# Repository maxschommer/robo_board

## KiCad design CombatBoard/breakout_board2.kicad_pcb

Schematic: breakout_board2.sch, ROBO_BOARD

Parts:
BTN1: CKN10291CT-ND; KMT071_NGJ_LHS
C1, C2: 10pF; C_0603
C3, C5, C13, C14, C15, C16: 1uF; C_0603
C4: 4.7uF, 16V; C_0805
C6: .1uF; C_0603
C7, C9, C10: 100nF; C_0603
C8, C11, C12: 10uF; C_0805
J1, J2: Conn_01x15; Pin_Header_Straight_1x15_Pitch2.54mm
J3: CONN_02x04; Pin_Header_Straight_2x04_Pitch2.54mm_SMD
J4: CONN_01X03; Pin_Header_Straight_1x03_Pitch2.54mm
J5: Conn_02x03_Odd_Even; Pin_Header_Straight_2x03_Pitch2.54mm
J6: Conn_01x02; Pin_Header_Straight_1x02_Pitch2.54mm
J7: Conn_01x04; Pin_Header_Straight_1x04_Pitch2.54mm
LED1: RED; LED_0805
LED2: GREEN; LED_0805
LED3: BLUE; LED_0805
OS1: 16MHZ; XC2119CT
R1: 10K; R_0603
R2, R3, R4: 499; R_0603
U1: ATMEGA328P-MUR; QFN-32-1EP_5x5mm_Pitch0.5mm
U2: TB6612FNG; SOP65P760X160-24N
U3: ADP3330; SOT-23-6
U4: LP5907SNX-3.3/NOPB; DQN4

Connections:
+3V3: C7.1, C8.1, C16.1, J2.14, J3.7 (Pin_4), U4.1
+5V: C3.2, C4.2, C5.2, C10.1, C12.1, C13.1, C15.1, J2.4, J5.2, R1.1, R4.2, U1.4, U1.6, U1.18, U2.15, U2.20, U2.23, U3.1, U4.3, U4.4
+12V: C9.1, C11.1, C14.1, J2.1, J6.1, U2.13, U2.14, U2.24, U3.2, U3.6
/A0: J2.12, U1.23
/A1: J2.11, U1.24
/A2: J2.10, U1.25
/A3: J2.9, U1.26
/A4: J2.8, U1.27
/A5: J2.7, U1.28
/A6: J2.6, U1.19
/A7: J2.5, U1.22
/AREF: C6.2, J2.13, U1.20
/D0: J1.2, U1.30
/D1: J1.1, U1.31
/D2: J1.5, R2.2, U1.32
/D3: J1.6, U1.1, U2.16
/D4: J1.7, U1.2
/D5: J1.8, U1.9, U2.17
/D6: J1.9, U1.10, U2.22
/D7: J1.10, J3.6, U1.11
/D8: J1.11, J3.5 (Pin_3), U1.12
/D9: J1.12, U1.13, U2.21
/D10: J1.13, J4.3, U1.14
/D11/MOSI: J1.14, J3.3 (Pin_2), J5.4, U1.15
/D12/MISO: J1.15, J3.2 (Pin_8), J5.1, U1.16
/D13/SCK: J2.15, J3.4 (Pin_7), J5.3, R3.1, U1.17
/M1A: J7.4, U2.11, U2.12
/M1B: J7.3, U2.7, U2.8
/M2A: J7.2, U2.5, U2.6
/M2B: J7.1, U2.1, U2.2
/RESET: BTN1.2, J1.3, J2.3, J5.5, R1.2, U1.29, U2.19
GND: BTN1.3, C1.2, C2.2, C3.1, C4.1, C5.1, C6.1, C7.2, C8.2, C9.2, C10.2, C11.2, C12.2, C13.2, C14.2, C15.2, C16.2, J1.4, J2.2, J3.8 (Pin_5), J4.1, J5.6, J6.2, LED1.1, LED2.1, LED3.1, OS1.2, OS1.4, U1.3, U1.5, U1.21, U1.33, U2.3, U2.4, U2.9, U2.10, U2.18, U3.4, U4.2, U4.5
unnamed: C1.1, OS1.1, U1.8
unnamed: C2.1, OS1.3, U1.7
unnamed: LED1.2, R3.2
unnamed: LED2.2, R2.1
unnamed: LED3.2, R4.1

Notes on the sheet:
BLDC HEADER
NRF24L01 HEADER
ICSP HEADER
5V REGULATOR
3V3 REGULATOR
DC MOTOR CONTROLLER
MICROCONTROLLER
VIN
POWER LED
RADIO LED

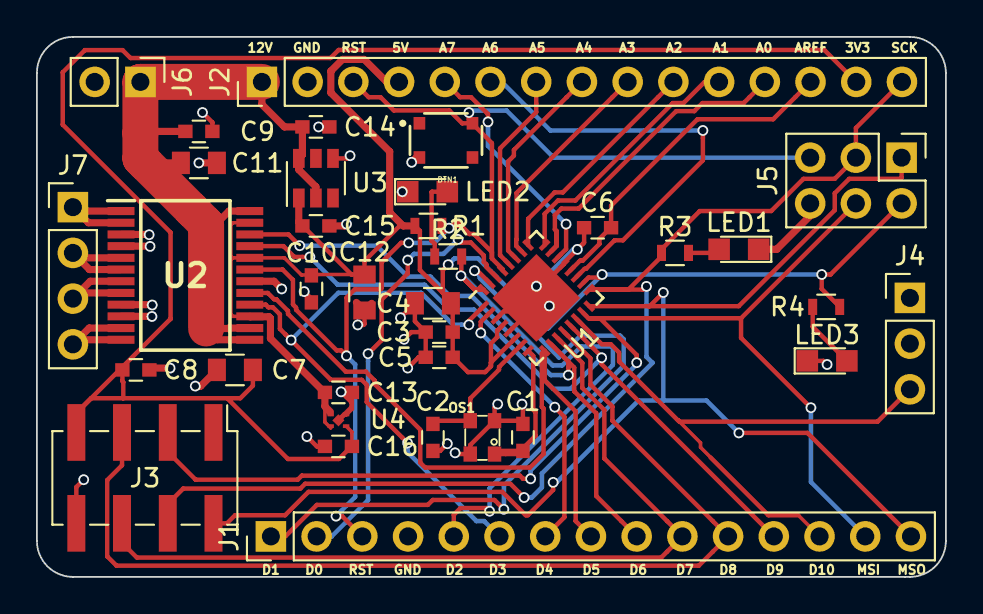
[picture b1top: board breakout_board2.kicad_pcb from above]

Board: 2 copper layers, 50.5 x 30.0 mm, 36 parts (0 on the bottom side), 37 nets.

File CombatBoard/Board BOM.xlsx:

Component | Description | Part | References | Value | Digikey P/N | Quantity Per PCB | Cost | Line Cost
1.0 | Reset Button | button | BTN1 | CKN10291CT-ND | CKN10291CT-ND | 1.0 | 0.3 | 0.3
2.0 | Unpolarized capacitor , .1uf | C | C6 C7 C9 C10 | .1uF | 445-5667-1-ND | 4.0 | 0.1 | 0.4 | 311-1779-1-ND
3.0 | Unpolarized capacitor, 10pf | C | C1 C2 | 10pF | 490-9682-1-ND | 2.0 | 0.15 | 0.3
4.0 | Unpolarized capacitor, 10uf | C | C8 C11 C12 | 10uF | 445-5667-1-ND | 3.0 | 0.28 | 0.84 | 1276-2872-1-ND
5.0 | Unpolarized capacitor, 1uf | C | C3 C5 C13 C14 C15 C16 | 1uF | 399-7376-1-ND | 6.0 | 0.24 | 1.44
6.0 | Unpolarized capacitor,16v 4.7uf | C | C4 | 4.7uF, 16V | 587-4877-1-ND | 1.0 | 0.34 | 0.34
7.0 | BLDC Pin Header | Conn_01x03 | J4 | CONN_01X03 | S5674-ND | 1.0 | 1.14 | 1.14
8.0 | Radio Pin HEader | Conn_02x04_Counter_Clockwise-RESCUE-breakout_board | J3 | CONN_02x04 | ----- | 1.0 | 0.0 | 0
9.0 | ICSP Pin Header | Conn_02x03_Odd_Even | J5 | Conn_02x03_Odd_Even | ------ | 1.0 | 0.0 | 0
10.0 | LED generic | LED | LED3 | BLUE | 160-1579-1-ND | 1.0 | 0.43 | 0.43
11.0 | LED generic | LED | LED2 | GREEN | 160-1887-1-ND | 1.0 | 0.65 | 0.65
12.0 | LED generic | LED | LED1 | RED | 160-1427-1-ND | 1.0 | 0.31 | 0.31
13.0 | 16MHZ Oscillator | Crystal_GND24 | OS1 | 16MHZ | XC2119CT-ND | 1.0 | 0.74 | 0.74
14.0 | Resistor 10K | R | R1 | 10K | 311-10.0KHRCT-ND | 1.0 | 0.1 | 0.1
15.0 | Resistor 499ohm | R | R2 R3 R4 | 499.0 | 311-499HRCT-ND | 3.0 | 0.1 | 0.3
16.0 | 5V Regulator | ADP3330 | U3 | ADP3330 | ADP3330ARTZ-5-RL7CT-ND | 1.0 | 2.64 | 2.64
17.0 | Logic Chip | ATMEGA328P-MUR | U1 | ATMEGA328P-MUR | ATMEGA328P-MURCT-ND | 1.0 | 2.2 | 2.2
18.0 | 3V3 Regulator | LP5907SNX-3.3/NOPB | U4 | LP5907SNX-3.3/NOPB | 296-39066-1-ND | 1.0 | 0.55 | 0.55
19.0 | Brushed Motor Driver | TB6612FNG | U2 | TB6612FNG | TB6612FNGC8ELCT-ND | 1.0 | 2.11 | 2.11
 |  |  |  |  |  |  | 14.79

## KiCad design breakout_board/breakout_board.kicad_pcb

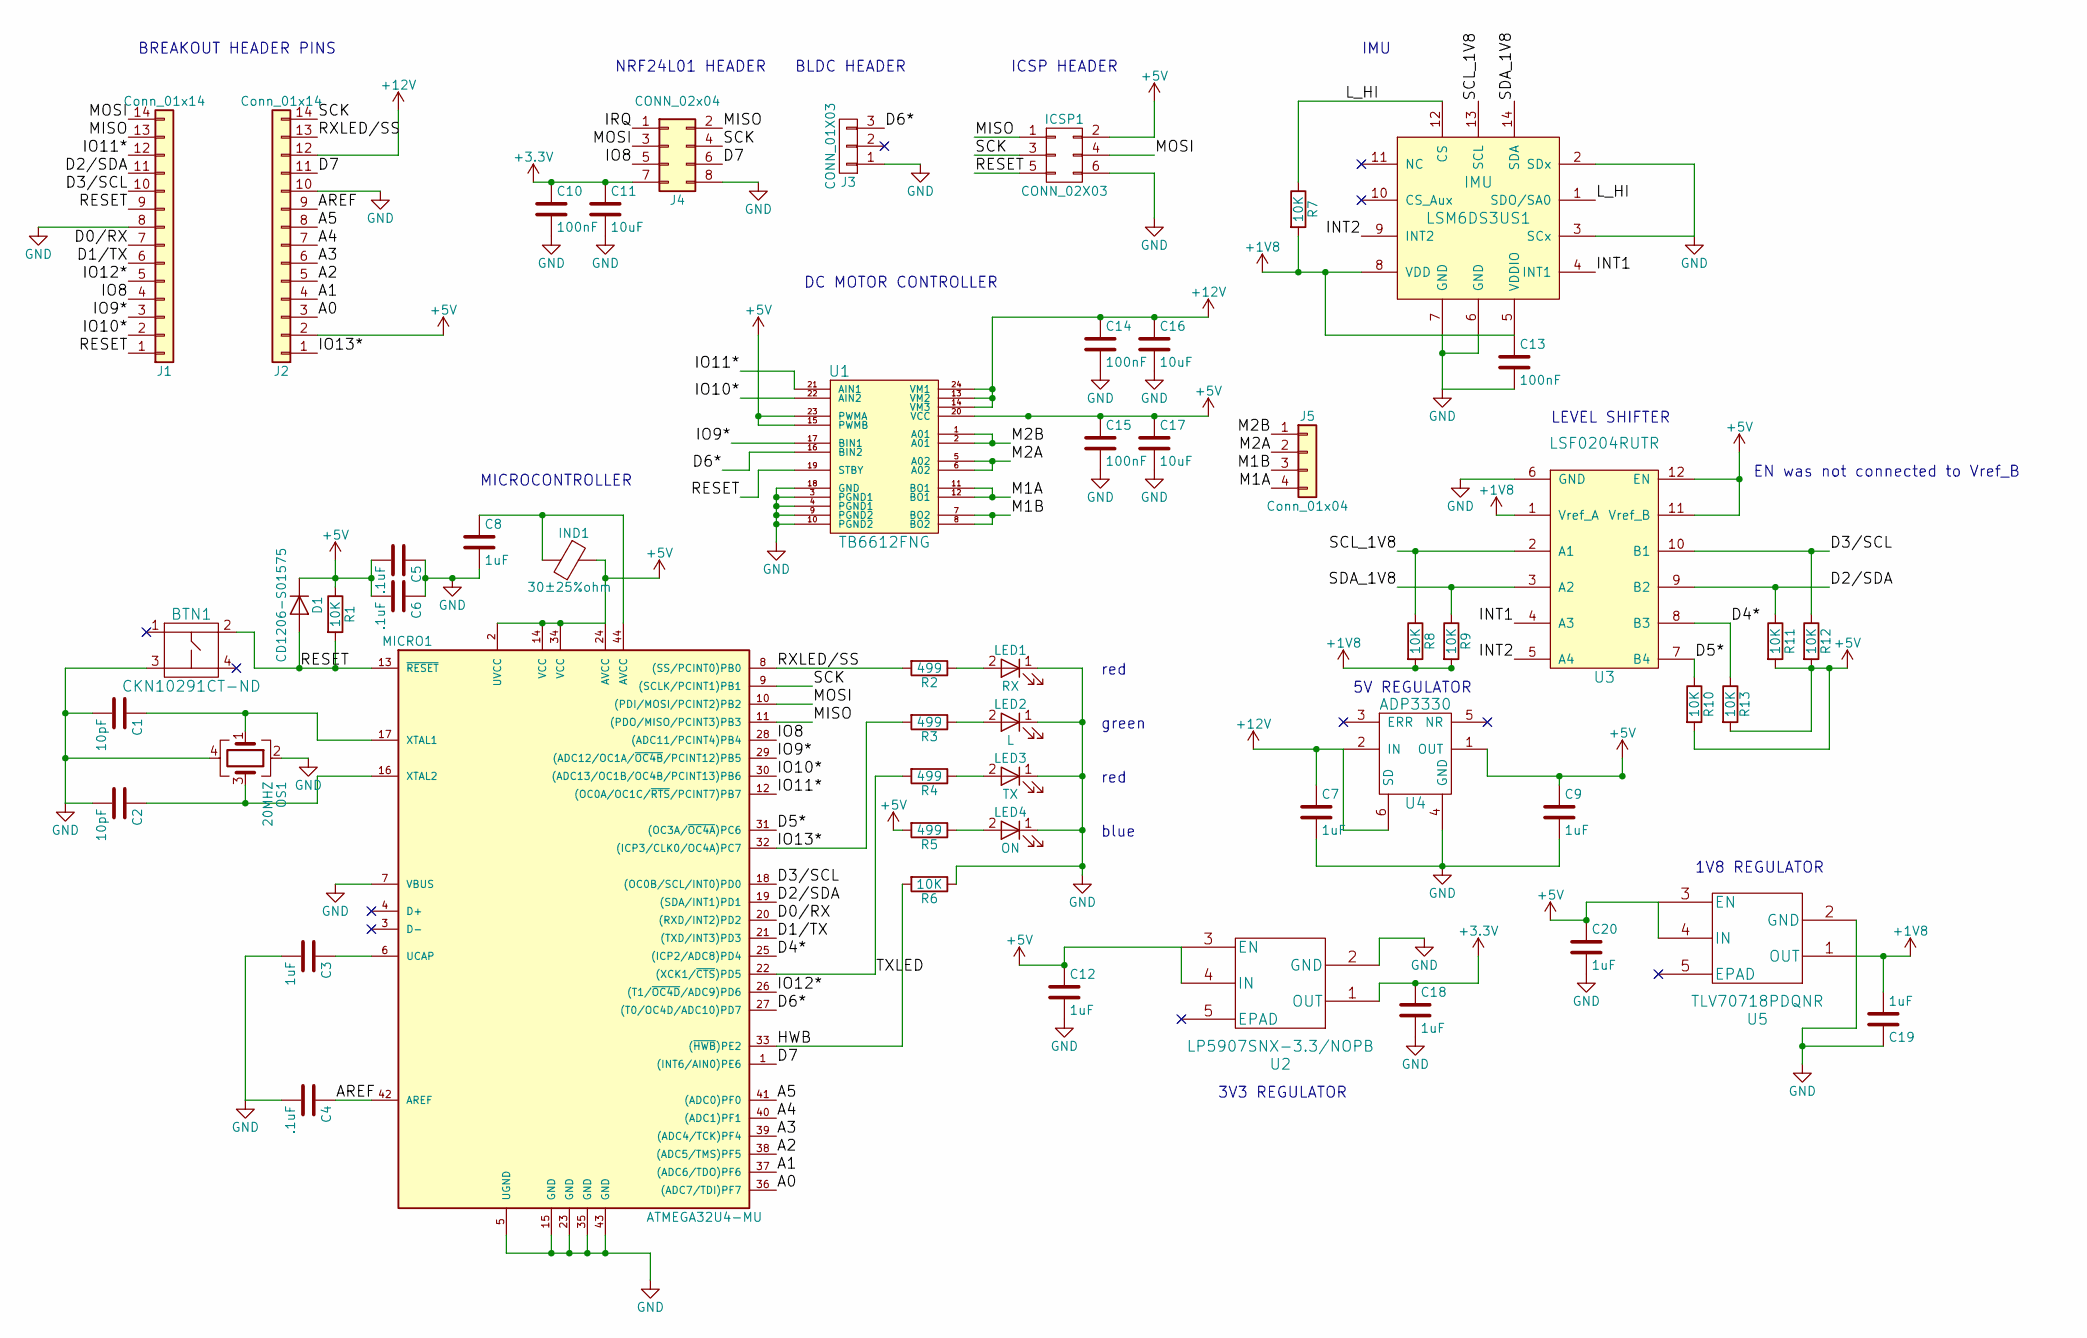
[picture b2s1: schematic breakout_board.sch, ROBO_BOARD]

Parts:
BTN1: CKN10291CT-ND; KMT071_NGJ_LHS
C1, C2: 10pF; C_0603
C3, C7, C8, C9, C12, C18, C19, C20: 1uF; C_0603
C4, C5, C6: .1uF; C_0603
C10, C13, C14, C15: 100nF; C_0603
C11, C16, C17: 10uF; C_0805
D1: CD1206-S01575; C_0402
ICSP1: CONN_02X03; Pin_Header_Straight_2x03_Pitch2.54mm
IND1: 30±25%ohm; L_0805
J1, J2: Conn_01x14; Pin_Header_Straight_1x14_Pitch2.54mm
J3: CONN_01X03; Pin_Header_Straight_1x03_Pitch2.54mm
J4: CONN_02x04; Pin_Header_Straight_2x04_Pitch2.54mm_SMD
J5: Conn_01x04; Pin_Header_Straight_1x04_Pitch2.54mm
LED1: RX; LED_0805
LED2: L; LED_0805
LED3: TX; LED_0805
LED4: ON; LED_0805
LSM6DS3US1: IMU; LGA-14L
MICRO1: ATMEGA32U4-MU; QFN-44-1EP_7x7mm_Pitch0.5mm
OS1: 20MHZ; ABM11AIG
R1, R6, R7, R8, R9, R10, R11, R12, R13: 10K; R_0603
R2, R3, R4, R5: 499; R_0603
U1: TB6612FNG; SOP65P760X160-24N
U2: LP5907SNX-3.3/NOPB; DQN4
U3: LSF0204RUTR; R-PUQFN-N12
U4: ADP3330; SOT-23-6
U5: TLV70718PDQNR; DQN4

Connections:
+1V8: C13.1, C19.2, LSM6DS3US1.5 (VDDIO), LSM6DS3US1.8 (VDD), R7.2, R8.2, R9.2, U3.1 (Vref_A), U5.1 (OUT)
+3V3: C10.1, C11.1, C18.1, J4.7 (Pin_4), U2.1 (OUT)
+5V: C5.2, C6.2, C9.1, C12.1, C15.1, C17.1, C20.1, D1.1 (K), ICSP1.2, IND1.1, J2.2, MICRO1.2 (UVCC), MICRO1.14 (VCC), MICRO1.24 (AVCC), MICRO1.34 (VCC), R1.1, R5.2, R10.2, R11.2, R12.2, R13.2, U1.15 (PWMB), U1.20 (VCC), U1.23 (PWMA), U2.3 (EN), U2.4 (IN), U3.11 (Vref_B), U3.12 (EN), U4.1 (OUT), U5.3 (EN), U5.4 (IN)
+12V: C7.1, C14.1, C16.1, J2.12, U1.13 (VM2), U1.14 (VM3), U1.24 (VM1), U4.2 (IN), U4.6 (SD)
/A0: J2.3, MICRO1.36 ((ADC7/TDI)PF7)
/A1: J2.4, MICRO1.37 ((ADC6/TDO)PF6)
/A2: J2.5, MICRO1.38 ((ADC5/TMS)PF5)
/A3: J2.6, MICRO1.39 ((ADC4/TCK)PF4)
/A4: J2.7, MICRO1.40 ((ADC1)PF1)
/A5: J2.8, MICRO1.41 ((ADC0)PF0)
/AREF: C4.1, J2.9, MICRO1.42 (AREF)
/D0/RX: J1.7, MICRO1.20 ((RXD/INT2)PD2)
/D1/TX: J1.6, MICRO1.21 ((TXD/INT3)PD3)
/D2/SDA: J1.11, MICRO1.19 ((SDA/INT1)PD1), R11.1, U3.9 (B2)
/D3/SCL: J1.10, MICRO1.18 ((OC0B/SCL/INT0)PD0), R12.1, U3.10 (B1)
/D4*: MICRO1.25 ((ICP2/ADC8)PD4), R13.1, U3.8 (B3)
/D5*: MICRO1.31 ((OC3A/~OC4A~)PC6), R10.1, U3.7 (B4)
/D6*: J3.3, MICRO1.27 ((T0/OC4D/ADC10)PD7), U1.16 (BIN2)
/D7: J2.11, J4.6, MICRO1.1 ((INT6/AIN0)PE6)
/HWB: MICRO1.33 ((~HWB~)PE2), R6.2
/INT1: LSM6DS3US1.4 (INT1), U3.4 (A3)
/INT2: LSM6DS3US1.9 (INT2), U3.5 (A4)
/IO8: J1.4, J4.5 (Pin_3), MICRO1.28 ((ADC11/PCINT4)PB4)
/IO9*: J1.3, MICRO1.29 ((ADC12/OC1A/~OC4B~/PCINT12)PB5), U1.17 (BIN1)
/IO10*: J1.2, MICRO1.30 ((ADC13/OC1B/OC4B/PCINT13)PB6), U1.22 (AIN2)
/IO11*: J1.12, MICRO1.12 ((OC0A/OC1C/~RTS~/PCINT7)PB7), U1.21 (AIN1)
/IO12*: J1.5, MICRO1.26 ((T1/~OC4D~/ADC9)PD6)
/IO13*: J2.1, MICRO1.32 ((ICP3/CLK0/OC4A)PC7), R3.2
/IRQ: J4.1
/L_HI: LSM6DS3US1.1 (SDO/SA0), LSM6DS3US1.12 (CS), R7.1
/M1A: J5.4, U1.11 (BO1), U1.12 (BO1)
/M1B: J5.3, U1.7 (BO2), U1.8 (BO2)
/M2A: J5.2, U1.5 (A02), U1.6 (A02)
/M2B: J5.1, U1.1 (A01), U1.2 (A01)
/MISO: ICSP1.1, J1.13, J4.2 (Pin_8), MICRO1.11 ((PDO/MISO/PCINT3)PB3)
/MOSI: ICSP1.4, J1.14, J4.3 (Pin_2), MICRO1.10 ((PDI/MOSI/PCINT2)PB2)
/RESET: BTN1.2, D1.2 (A), ICSP1.5, J1.1, J1.9, MICRO1.13 (~RESET~), R1.2, U1.19 (STBY)
/RXLED/SS: J2.13, MICRO1.8 ((SS/PCINT0)PB0), R2.2
/SCK: ICSP1.3, J2.14, J4.4 (Pin_7), MICRO1.9 ((SCLK/PCINT1)PB1)
/SCL_1V8: LSM6DS3US1.13 (SCL), R8.1, U3.2 (A1)
/SDA_1V8: LSM6DS3US1.14 (SDA), R9.1, U3.3 (A2)
/TXLED: MICRO1.22 ((XCK1/~CTS~)PD5), R4.2
GND: BTN1.3, C1.2, C2.2, C3.2, C4.2, C5.1, C6.1, C7.2, C8.2, C9.2, C10.2, C11.2, C12.2, C13.2, C14.2, C15.2, C16.2, C17.2, C18.2, C19.1, C20.2, ICSP1.6, J1.8, J2.10, J3.1, J4.8 (Pin_5), LED1.1 (K), LED2.1 (K), LED3.1 (K), LED4.1 (K), LSM6DS3US1.2 (SDx), LSM6DS3US1.3 (SCx), LSM6DS3US1.6 (GND), LSM6DS3US1.7 (GND), MICRO1.5 (UGND), MICRO1.7 (VBUS), MICRO1.15 (GND), MICRO1.23 (GND), MICRO1.35 (GND), MICRO1.43 (GND), OS1.2, OS1.4, R6.1, U1.3 (PGND1), U1.4 (PGND1), U1.9 (PGND2), U1.10 (PGND2), U1.18 (GND), U2.2 (GND), U3.6 (GND), U4.4 (GND), U5.2 (GND)
unnamed: C1.1, MICRO1.17 (XTAL1), OS1.1
unnamed: C2.1, MICRO1.16 (XTAL2), OS1.3
unnamed: C3.1, MICRO1.6 (UCAP)
unnamed: C8.1, IND1.2, MICRO1.44 (AVCC)
unnamed: LED1.2 (A), R2.1
unnamed: LED2.2 (A), R3.1
unnamed: LED3.2 (A), R4.1
unnamed: LED4.2 (A), R5.1

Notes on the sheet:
red
green
blue
BLDC HEADER
NRF24L01 HEADER
ICSP HEADER
5V REGULATOR
3V3 REGULATOR
1V8 REGULATOR
LEVEL SHIFTER
IMU
DC MOTOR CONTROLLER
MICROCONTROLLER
BREAKOUT HEADER PINS
EN was not connected to Vref_B

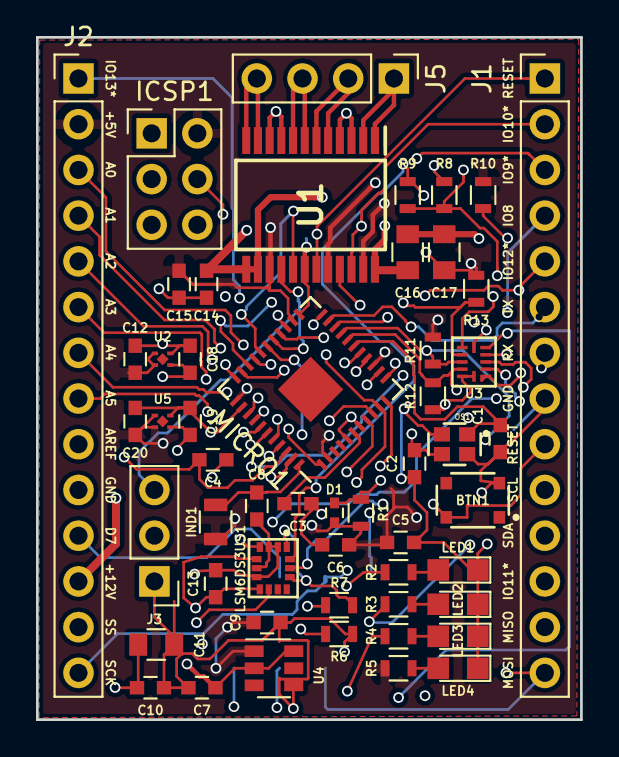
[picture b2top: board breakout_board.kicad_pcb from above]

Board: 4 copper layers, 30.2 x 37.9 mm, 54 parts (1 on the bottom side), 50 nets.

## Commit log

2017-09-28 Adding atmega partial schematic
2017-09-28 Added some capacitors
2017-09-30 Added IMU
2017-10-01 Added brushed motor driver and headers
2017-10-01 Fixed trash labeling and remade ugly garbage while changing capacitors and resistors to be correct
2017-10-01 Added submission files
2017-10-05 Made changes from Brad
2017-10-10 Made some footprints
2017-10-10 Footprinting done - needs checking.
2017-10-11 More done
2017-10-11 worked some more
2017-10-12 Changed components, routed a bunch of stuff
2017-10-13 Finished the board layout
2017-10-13 Finished foreal
2017-11-27 Fixed board
2017-11-27 did DRC
2018-01-15 started altium redesign
    How to edit the title block tho? Nobody knows.
2018-01-15 started sourcing/adding components
    snapeda is saving my liiife
2018-01-24 redesign in work
    library management pending
2018-01-24 Added Libraries
2018-01-25 made kicad v2
    ditched altium due to poor generic component libraries (depends heavily
    on vault), doing a 2-layer layout.
2018-01-27 Finished board v2
2018-01-31 minot updates
